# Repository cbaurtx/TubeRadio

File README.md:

# TubeRadio
## Disclaimer
It is entirely your responsibility to comply with all 
applicable laws when possesing or operating this radio.
It is entirely your responsibility to make sure the all circuits, including the powersupply are operated safely.
## License
TubeRadio is covered by CERN-OHL-W (Weakly reciprocal) 
Refer to doc/LICENSE.md for the license text
## Notes
### Output Transformer
There is a DC bias flowing through the output transformer. To avoid magnetic saturation of the iron core the core needs a small paper/plastic gap (~0.1–0.3 mm) between E and I laminations of the E I core. Do not use a power
transformer or an audio transformer or a push pull amplifier.
### Anode Choke
Similar to the output transformer the anode choke L4 has a DC bias current. So this choke needs
a similar air gap as the output transformer to avoid magnetic saturation of the iron core.

### Input Tank and Tickler Coil
The target frequency range of this radio is from 1.50MHz to 4.25MHz. With a capacity of 70pF to 570pF we can calculate the inductance of the coil of the input tank.

**f₀ = 1 / (2π × √(L × C))**

**f₀** is the resonance frequency in hertz (Hz)

**L** is the inductance in henrys (H)

**C** is the capacitance in farads (F)

To get the calculted inductance of 20µH the input tank 
coil we need this air coil:

|Entity |Value|Unit|
|-------|-----|----|
|Turns  |25   |#   |
|Layers |2    |#   |
|Inner ø|13   |mm  |
|Wire ø |0.9  |mm  |

The antenna and the tickler coil both have 8 turns.
The antenna coil is wound on top of the input tank coil and the tickler coil is side by side of the other coils at a distance of 10mm.

The design files are for KiCad version 9.

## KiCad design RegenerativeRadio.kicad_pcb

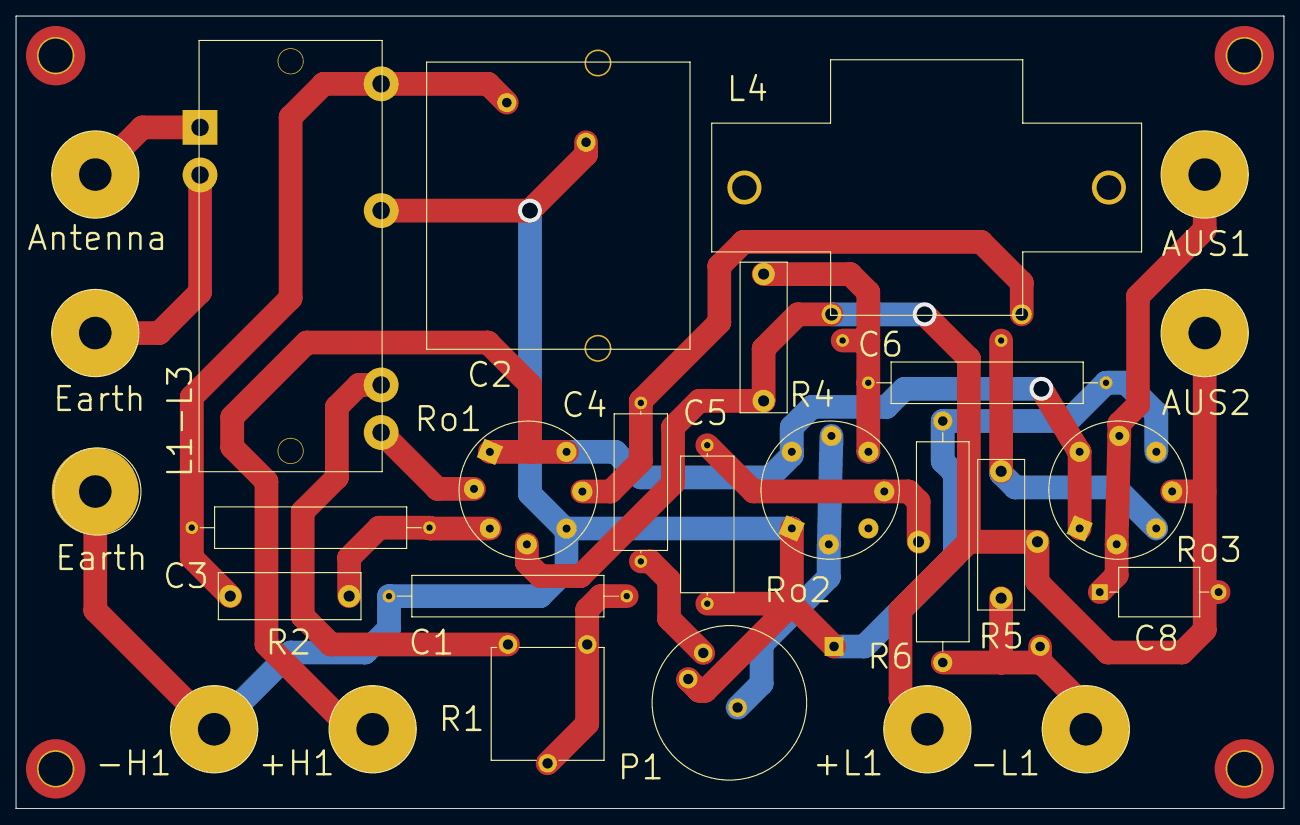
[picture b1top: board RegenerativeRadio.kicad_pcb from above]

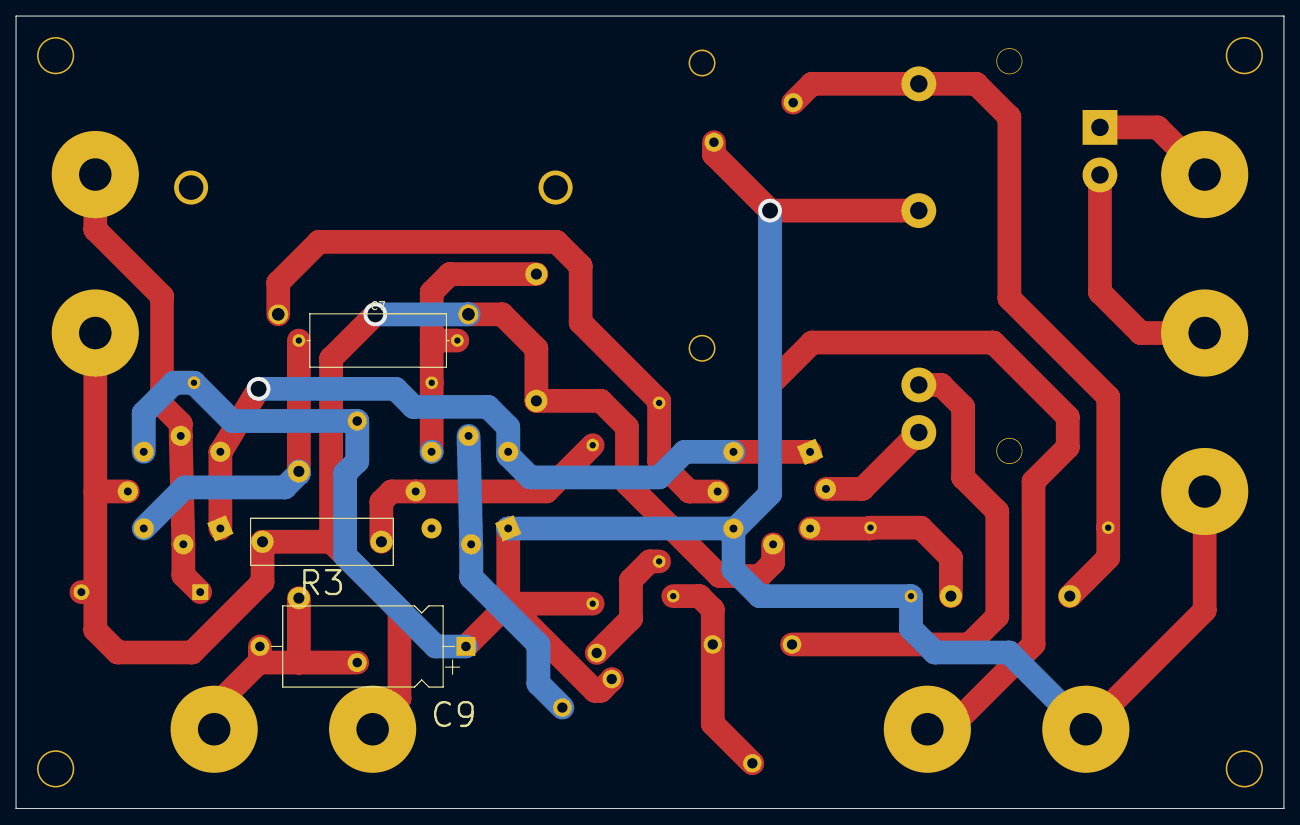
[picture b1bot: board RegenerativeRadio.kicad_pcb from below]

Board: 2 copper layers, 160.0 x 100.0 mm, 34 parts (3 on the bottom side), 18 nets.

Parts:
+H1: Conn_01x01_Female; Banana_Jack_Terminal_1Pin
+L1: Conn_01x01_Female; Banana_Jack_Terminal_1Pin
-H1: Conn_01x01_Female; Banana_Jack_Terminal_1Pin
-L1: Conn_01x01_Female; Banana_Jack_Terminal_1Pin
ANTENNE1: Conn_01x01_Female; Banana_Jack_Terminal_1Pin
AUS1, AUS2: Conn_01x01_Female; Banana_Jack_Terminal_1Pin
C1, C3, C6: 270pF; C_Axial_L25.0mm_D5.0mm_P30.00mm_Horizontal
C2: 360pF; C_Var_L36mm_W33mm
C4, C5, C7: 39nF; C_Axial_L17.0mm_D6.5mm_P20.00mm_Horizontal
C8: 10nF; C_Axial_L10.0mm_D6.0mm_P15.00mm_Horizontal
C9: 47µF; CP_Axial_L20.0mm_D10.0mm_P26.00mm_Horizontal
E1: Erde; Banana_Jack_Terminal_1Pin
ERDE1: Conn_01x01_Female; Banana_Jack_Terminal_1Pin
H1, H2, H3, H4: MountingHole_Pad; MountingHole_4.3mm_M4_DIN965_Pad_TopOnly
L1-L3: Koppelspule; L_Antennal_L72mm_D23mm
L4: 10H; L_37mmx15mm
P1: 500kΩ; Potentiometer_Round_D19_Vertical
R1: 10kΩ; Potentiometer_ACP_CA14V-15_Vertical
R2, R3: 2MΩ; R_Vintage_17mm_D7mm_P15mm_Horizontal
R4: 270kΩ; R_Vintage_17mm_D7mm_P16mm_Horizontal
R5: 300kΩ; R_Vintage_17mm_D7mm_P16mm_Horizontal
R6: 300Ω; R_Axial_Power_L25.0mm_W6.4mm_P30.48mm
Ro1, Ro3: 2P2; Valve_Mini_P
Ro2: 1B2; Valve_Mini_P

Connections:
unnamed: +H1.1, Ro1.1, Ro1.7, Ro2.7, Ro3.1, Ro3.7
unnamed: +L1.1, AUS2.1, C8.2, L4.1, R3.2, R4.2, Ro1.4, Ro3.4
unnamed: -H1.1, C1.2, C2.2, C5.2, C6.2, C9.1, E1.1, L1-L3.6, P1.3, R6.1, Ro1.5, Ro2.1, Ro3.5
unnamed: -L1.1, C9.2, R5.2, R6.2
unnamed: ANTENNE1.1, L1-L3.1
unnamed: AUS1.1, C8.1, Ro3.2, Ro3.6
unnamed: C1.1, R1.2, R1.3
unnamed: C2.1, C3.2, L1-L3.5, R2.1
unnamed: C3.1, R2.2, Ro1.3
unnamed: C4.1, L4.2, Ro1.6
unnamed: C4.2, P1.1
unnamed: C5.1, R3.1, Ro2.4
unnamed: C6.1, C7.2, R4.1, Ro2.5
unnamed: C7.1, R5.1, Ro3.3
unnamed: ERDE1.1, L1-L3.2
unnamed: L1-L3.3, R1.1
unnamed: L1-L3.4, Ro1.2
unnamed: P1.2, Ro2.6

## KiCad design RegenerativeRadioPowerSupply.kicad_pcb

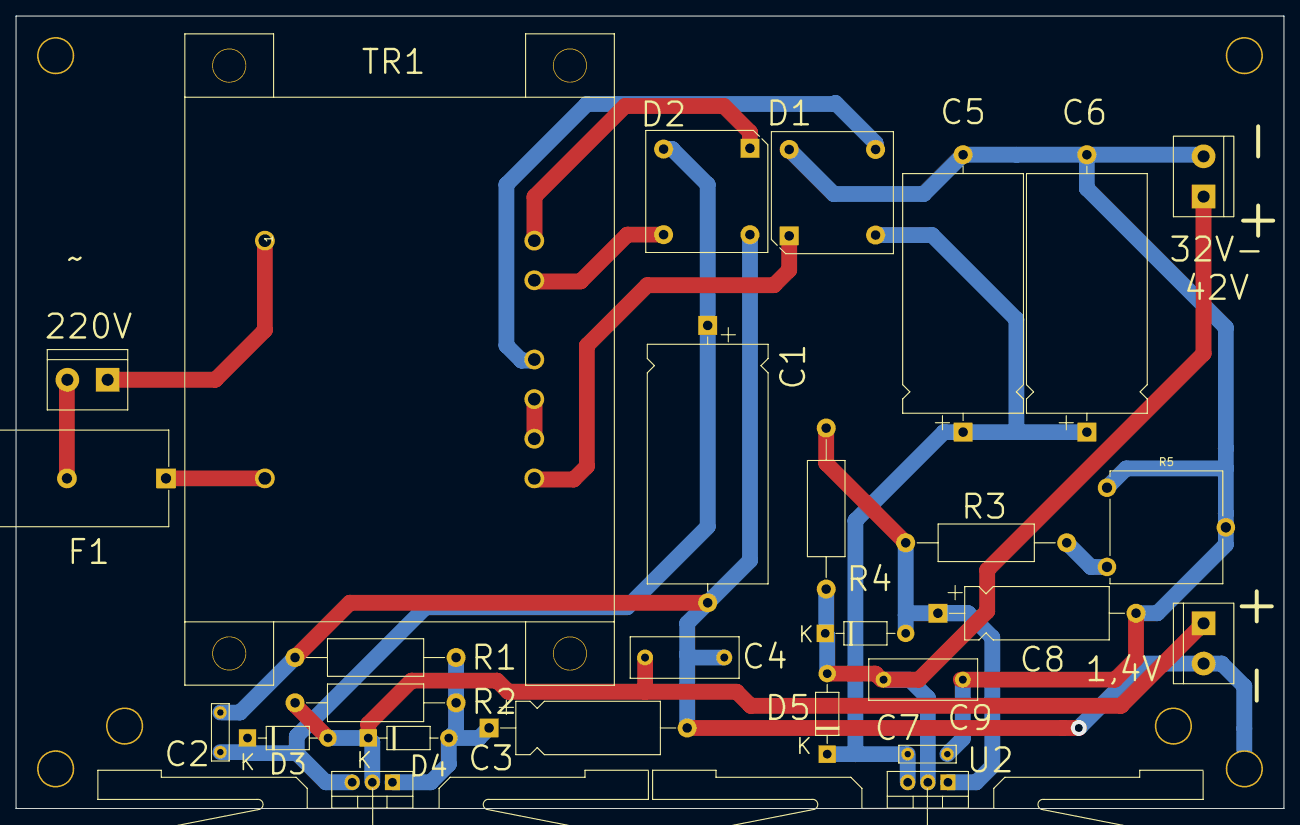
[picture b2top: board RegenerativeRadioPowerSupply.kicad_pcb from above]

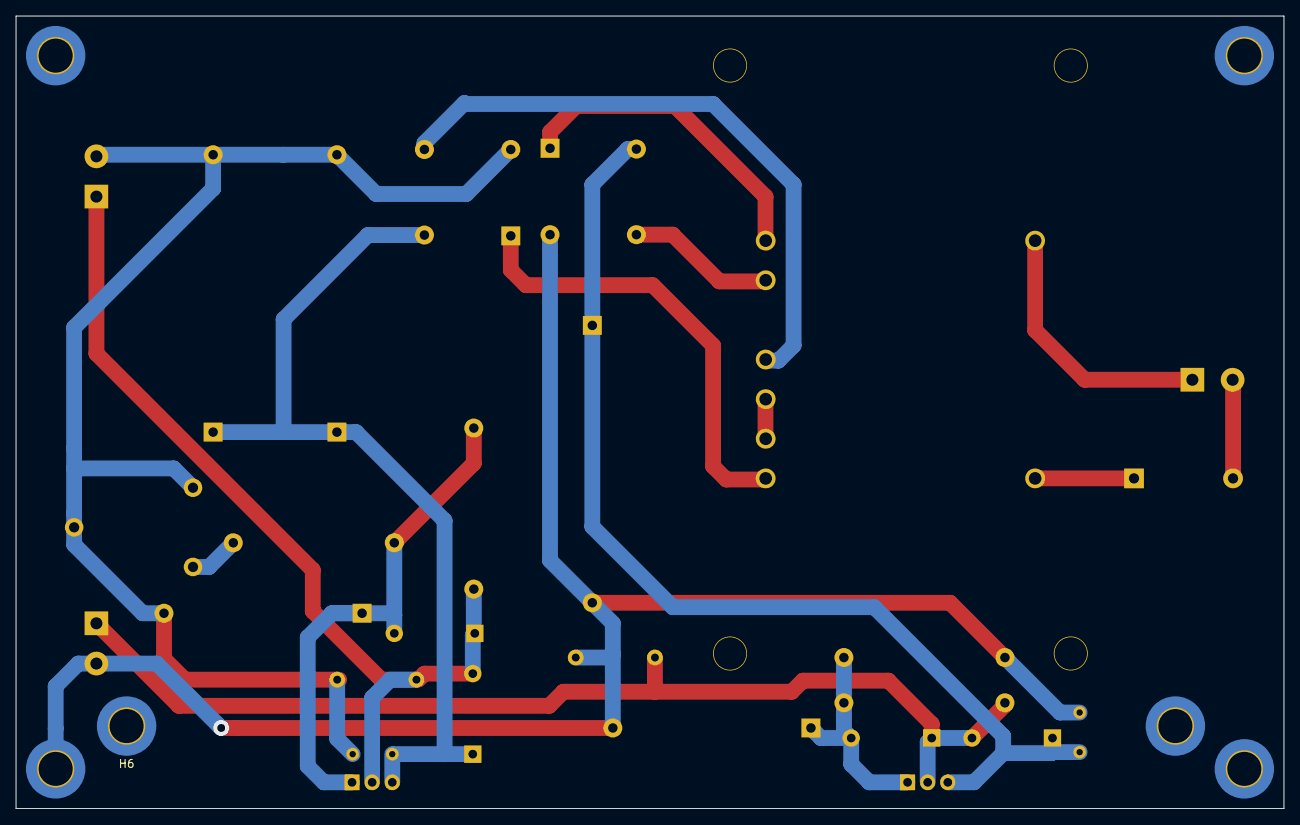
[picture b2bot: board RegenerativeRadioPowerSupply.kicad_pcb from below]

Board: 2 copper layers, 160.0 x 100.0 mm, 35 parts (6 on the bottom side), 17 nets.

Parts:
C1: 1000µF; CP_Axial_L30.0mm_D15.0mm_P35.00mm_Horizontal
C2, C7: 0.1µF; C_Rect_L7.0mm_W2.0mm_P5.00mm
C3, C8: 22µF; CP_Axial_L18.0mm_D6.5mm_P25.00mm_Horizontal
C4, C9: 1µF; C_Rect_L13.5mm_W5.0mm_P10.00mm_FKS3_FKP3_MKS4
C5, C6: 470µF 63V; CP_Axial_L30.0mm_D15.0mm_P35.00mm_Horizontal
D1, D2: B40C2300-1500B; Diode_Bridge_15.1x15.1x6.3mm_P10.9mm
D3, D4, D5, D6: 1N4004; D_DO-41_SOD81_P10.16mm_Horizontal
F1: 0.3A; Fuseholder_Cylinder-5x20mm
H1, H2, H3, H4, H5, H6: MountingHole_Pad; MountingHole_4.3mm_M4_DIN965_Pad_TopOnly
HS1, HS2: Heatsink; Heartsink_TO220_ver
J1: Screw_Terminal_01x02; TerminalBlock_bornier-2_P5.08mm
J2: H; TerminalBlock_bornier-2_P5.08mm
J3: L; TerminalBlock_bornier-2_P5.08mm
R1: 33Ω; R_Axial_DIN0414_L11.9mm_D4.5mm_P20.32mm_Horizontal
R2, R4: 270Ω; R_Axial_DIN0414_L11.9mm_D4.5mm_P20.32mm_Horizontal
R3: 6.8kΩ; R_Axial_DIN0414_L11.9mm_D4.5mm_P20.32mm_Horizontal
R5: 2.2kΩ; Potentiometer_ACP_CA14V-15_Vertical
TR1: TRANSF3; Transmformer_220V-18V_18V_9V
U1: LM317; TO-220-3_Vertical
U2: LM317HVT; TO-220-3_Vertical

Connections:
/ERDE: C1.2, C2.2, C3.2, C4.2, D2.4, H4.1, J2.2, R1.2
unnamed: C1.1, C2.1, D2.2, D3.1, U1.3
unnamed: C3.1, D4.2, R1.1, R2.1, U1.1
unnamed: C4.1, D3.2, D4.1, J2.1, R2.2, U1.2
unnamed: C5.1, C6.1, C7.1, D1.2, D5.1, U2.3
unnamed: C5.2, C6.2, C7.2, C8.2, C9.2, D1.4, J3.2, R5.2, R5.3
unnamed: C8.1, D6.2, R3.1, R4.1, U2.1
unnamed: C9.1, D5.2, D6.1, J3.1, R4.2, U2.2
unnamed: D1.1, TR1.3
unnamed: D1.3, TR1.6
unnamed: D2.1, TR1.8
unnamed: D2.3, TR1.7
unnamed: F1.1, TR1.2
unnamed: F1.2, J1.2
unnamed: J1.1, TR1.1
unnamed: R3.2, R5.1
unnamed: TR1.4, TR1.5

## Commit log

2025-05-16 MovedLICENSE.md to doc directory
2025-06-01 Update documentation, add LM317 simultion
2025-06-01 Update README.md
    Added section on anode choke L4
2025-06-01 Update RegenerativeRadio.kicad_sch
    Change value of anode choke L4. Inductance range is 6H to 10H.
2025-06-03 Added load to voltage regulator simulation
2025-06-03 Added PDF pf schematics
2025-06-03 Update README.md
    Fixed typo
